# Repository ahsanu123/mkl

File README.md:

# MKL

my kicad libraries

### Reference 

- [easyeda 2 kicad](https://github.com/uPesy/easyeda2kicad.py)
- [Pi Zero Template](https://github.com/vasya-zh/PiZeroHat/tree/main)

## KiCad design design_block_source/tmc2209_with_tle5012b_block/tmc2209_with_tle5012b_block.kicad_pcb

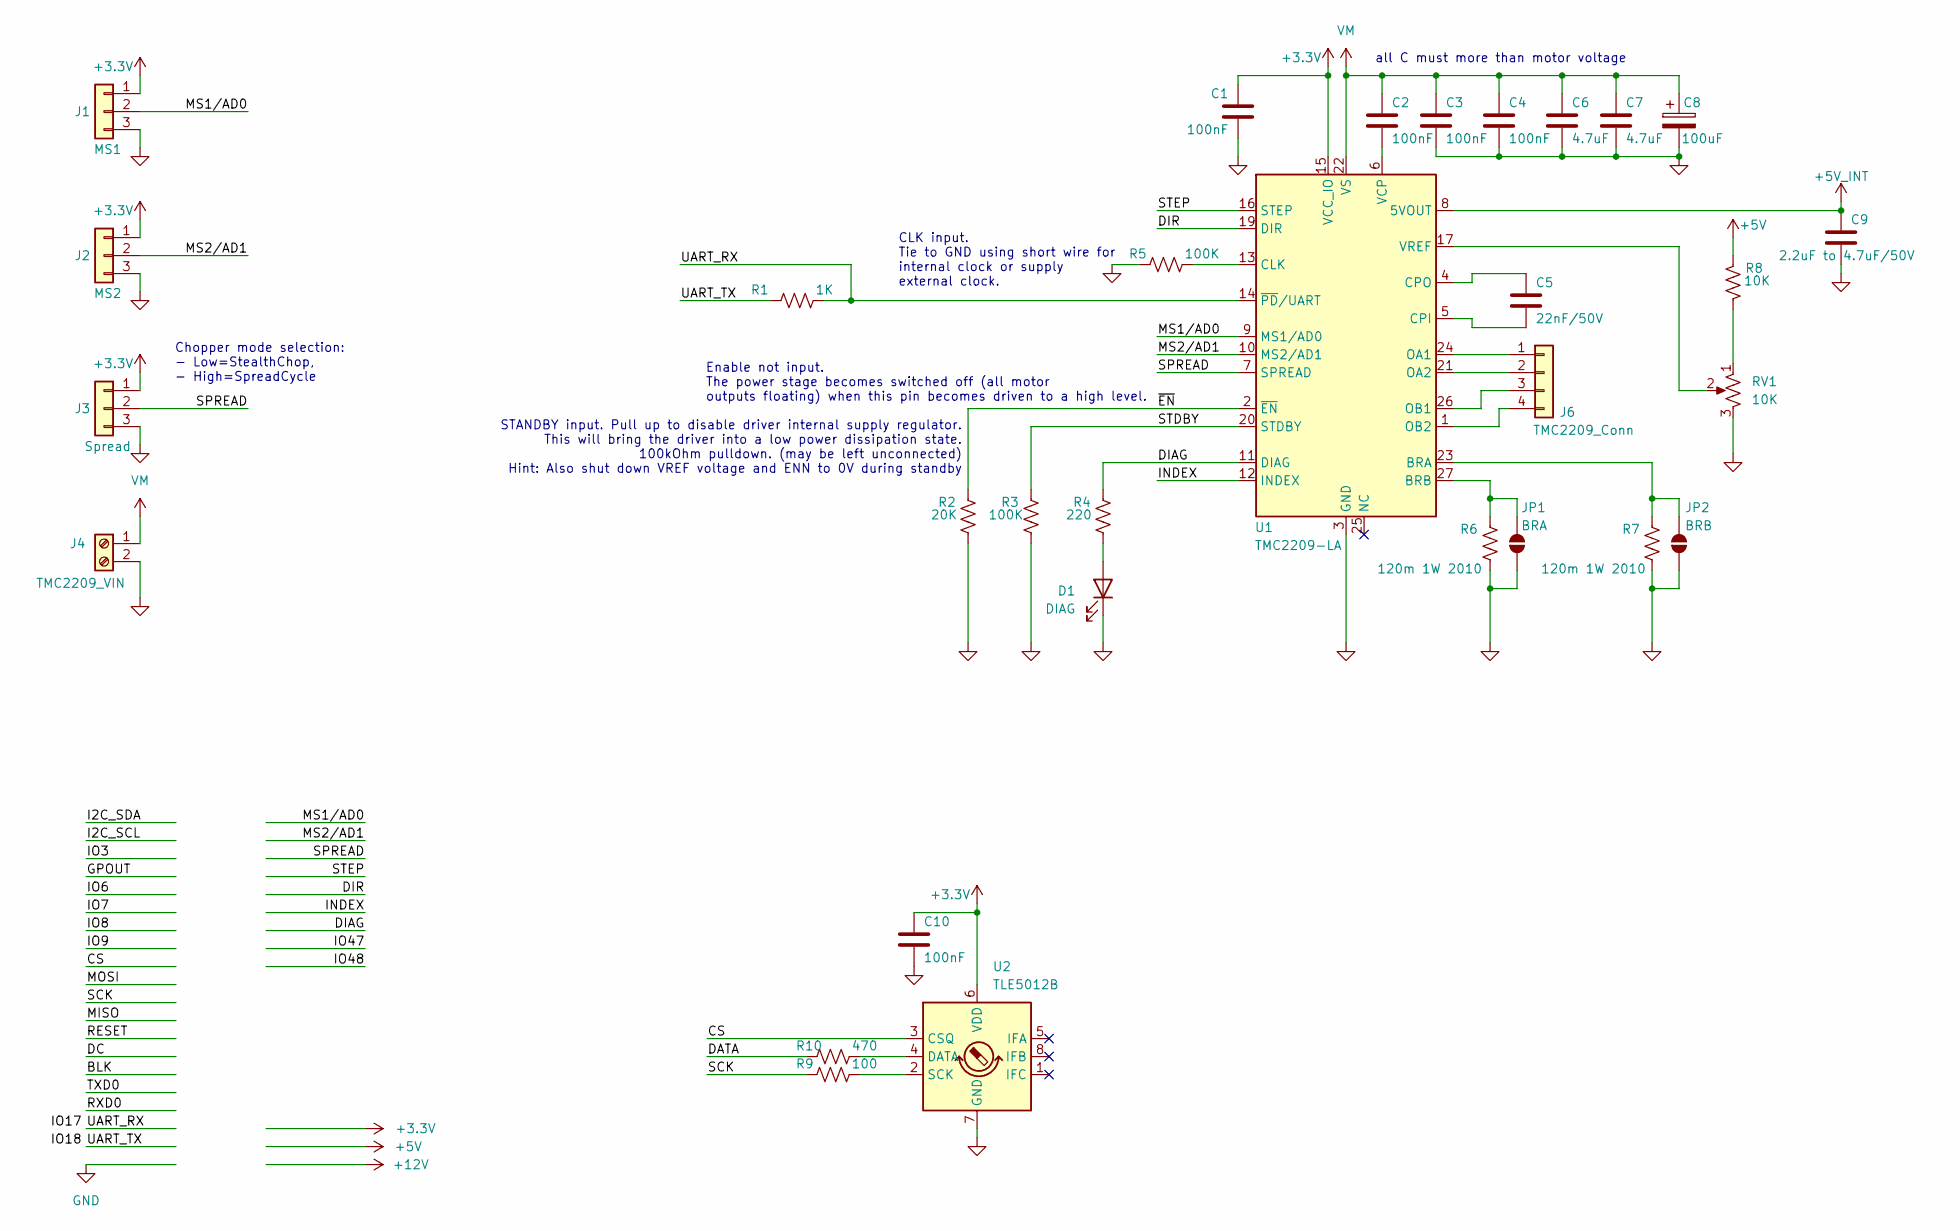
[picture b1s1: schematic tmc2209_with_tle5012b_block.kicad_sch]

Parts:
C1, C2, C3, C4, C10: 100nF; C_0805_2012Metric_Pad1.18x1.45mm_HandSolder
C5: 22nF/50V; C_0805_2012Metric_Pad1.18x1.45mm_HandSolder
C6, C7: 4.7uF; C_0805_2012Metric_Pad1.18x1.45mm_HandSolder
C8: 100uF; CP_Radial_D8.0mm_P3.50mm
C9: 2.2uF to 4.7uF/50V; C_0805_2012Metric_Pad1.18x1.45mm_HandSolder
D1: DIAG; LED_0805_2012Metric_Pad1.15x1.40mm_HandSolder
J1: MS1; PinHeader_1x03_P2.54mm_Vertical
J2: MS2; PinHeader_1x03_P2.54mm_Vertical
J3: Spread; PinHeader_1x03_P2.54mm_Vertical
J4: TMC2209_VIN; TerminalBlock_Phoenix_PT-1,5-2-5.0-H_1x02_P5.00mm_Horizontal
J6: TMC2209_Conn; Molex_Nano-Fit_105313-xx04_1x04_P2.50mm_Horizontal
JP1: BRA; SolderJumper-2_P1.3mm_Open_RoundedPad1.0x1.5mm
JP2: BRB; SolderJumper-2_P1.3mm_Open_RoundedPad1.0x1.5mm
R1: 1K; R_0805_2012Metric_Pad1.20x1.40mm_HandSolder
R2: 20K; R_0805_2012Metric_Pad1.20x1.40mm_HandSolder
R3, R5: 100K; R_0805_2012Metric_Pad1.20x1.40mm_HandSolder
R4: 220; R_0805_2012Metric_Pad1.20x1.40mm_HandSolder
R6, R7: 120m 1W 2010; R_2010_5025Metric
R8: 10K; R_0805_2012Metric_Pad1.20x1.40mm_HandSolder
R9: 100; R_0805_2012Metric_Pad1.20x1.40mm_HandSolder
R10: 470; R_0805_2012Metric_Pad1.20x1.40mm_HandSolder
RV1: 10K; Potentiometer_Bourns_3269W_Vertical
U1: TMC2209-LA; VQFN-28-1EP_5x5mm_P0.5mm_EP3.7x3.7mm
U2: TLE5012B; SOIC-8_3.9x4.9mm_P1.27mm

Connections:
+3.3V: C1.1, C10.1, J1.1, J2.1, J3.1, U1.15 (VCC_IO), U2.6 (VDD)
+5V: R8.1
+5V_INT: C9.1, U1.8 (5VOUT)
/CS: U2.3 (CSQ)
/DATA: R10.2
/DIAG: R4.1, U1.11 (DIAG)
/DIR: U1.19 (DIR)
/INDEX: U1.12 (INDEX)
/MS1/AD0: J1.2, U1.9 (MS1/AD0)
/MS2/AD1: J2.2, U1.10 (MS2/AD1)
/SCK: R9.2
/SPREAD: J3.2, U1.7 (SPREAD)
/STDBY: R3.1, U1.20 (STDBY)
/STEP: U1.16 (STEP)
/UART_RX: R1.1, U1.14 (~PD/UART)
/UART_TX: R1.2
/~EN: R2.1, U1.2 (~EN)
GND: C1.2, C3.2, C4.2, C6.2, C7.2, C8.2, C9.2, C10.2, D1.1 (K), J1.3, J2.3, J3.3, J4.2, JP1.1 (A), JP2.1 (A), R2.2, R3.2, R5.2, R6.2, R7.2, RV1.3, U1.3 (GND), U1.18 (GND), U1.29 (GND), U2.7 (GND)
unnamed: D1.2 (A), R4.2
unnamed: J6.1, U1.24 (OA1)
unnamed: J6.2, U1.21 (OA2)
unnamed: J6.3, U1.26 (OB1)
unnamed: J6.4, U1.1 (OB2)
unnamed: JP1.2 (B), R6.1, U1.27 (BRB)
unnamed: JP2.2 (B), R7.1, U1.23 (BRA)
unnamed: R8.2, RV1.1
unnamed: R5.1, U1.13 (CLK)
unnamed: C5.2, U1.5 (CPI)
unnamed: C5.1, U1.4 (CPO)
unnamed: C2.2, U1.6 (VCP)
unnamed: RV1.2, U1.17 (VREF)
unnamed: R10.1, U2.4 (DATA)
unnamed: R9.1, U2.2 (SCK)
VM: C2.1, C3.1, C4.1, C6.1, C7.1, C8.1, J4.1, U1.22 (VS), U1.28 (VS)

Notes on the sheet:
Chopper mode selection: - Low=StealthChop, - High=SpreadCycle
all C must more than motor voltage
Enable not input. The power stage becomes switched off (all motor outputs floating) when this pin becomes driven to a high level.
STANDBY input. Pull up to disable driver internal supply regulator. This will bring the driver into a low power dissipation state. 100kOhm pulldown. (may be left unconnected) Hint: Also shut down VREF voltage and ENN to 0V during standby
CLK input. Tie to GND using short wire for internal clock or supply external clock.

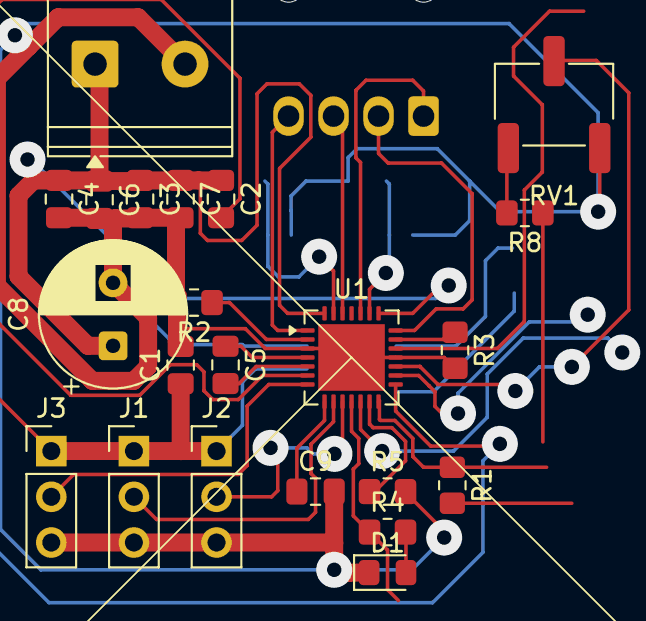
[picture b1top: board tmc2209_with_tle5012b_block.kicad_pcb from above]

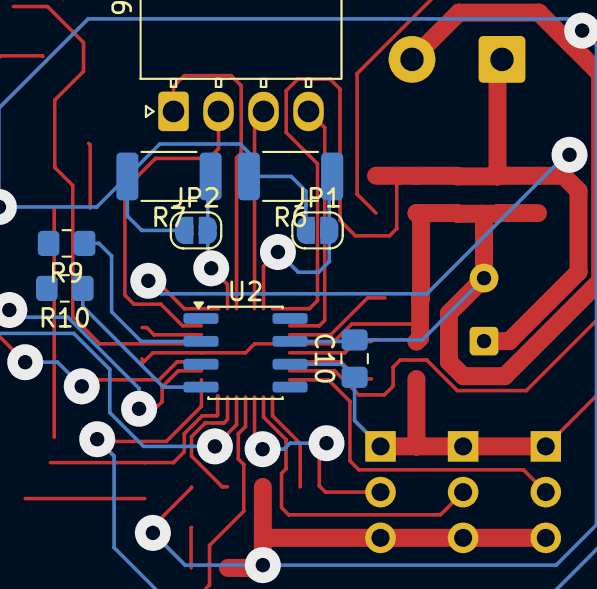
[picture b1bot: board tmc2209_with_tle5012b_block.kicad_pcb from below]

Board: 2 copper layers, 31 parts (9 on the bottom side), 26 nets.

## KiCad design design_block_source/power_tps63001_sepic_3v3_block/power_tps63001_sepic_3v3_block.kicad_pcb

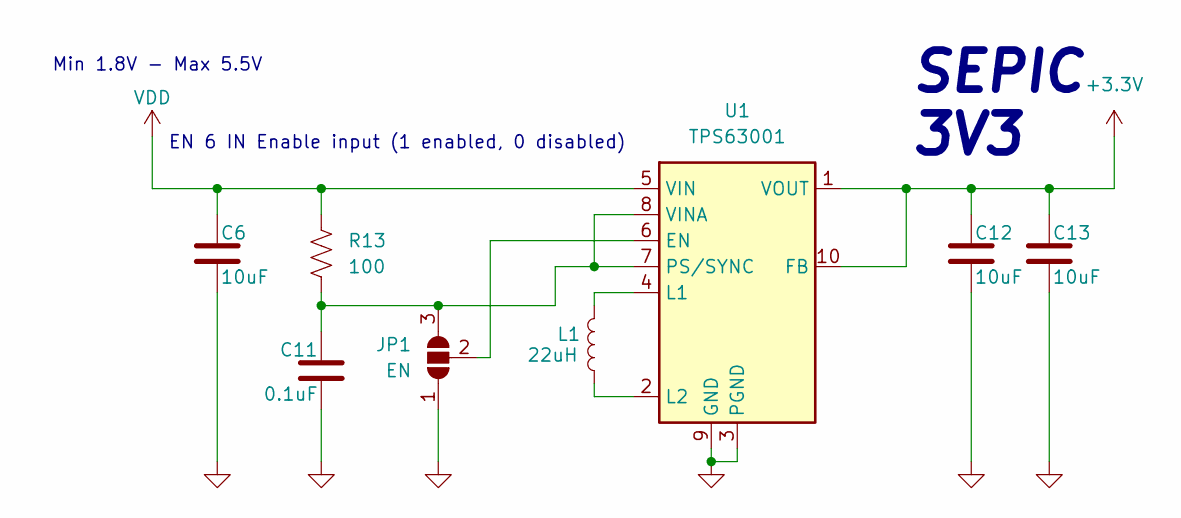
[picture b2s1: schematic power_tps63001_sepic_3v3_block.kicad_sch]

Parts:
C6, C12, C13: 10uF; C_0805_2012Metric_Pad1.18x1.45mm_HandSolder
C11: 0.1uF; C_0805_2012Metric_Pad1.18x1.45mm_HandSolder
JP1: EN; SolderJumper-3_P1.3mm_Open_RoundedPad1.0x1.5mm_NumberLabels
L1: 22uH; L_Bourns_SRP7028A_7.3x6.6mm
R13: 100; R_0805_2012Metric_Pad1.20x1.40mm_HandSolder
U1: TPS63001; Texas_DRC0010J_ThermalVias

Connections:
+3.3V: C12.1, C13.1, U1.1 (VOUT), U1.10 (FB)
GND: C6.2, C11.2, C12.2, C13.2, JP1.1 (A), U1.3 (PGND), U1.9 (GND), U1.11 (PGND)
unnamed: C11.1, JP1.3 (B), R13.2, U1.7 (PS/SYNC), U1.8 (VINA)
unnamed: JP1.2 (C), U1.6 (EN)
unnamed: L1.2, U1.4 (L1)
unnamed: L1.1, U1.2 (L2)
VDD: C6.1, R13.1, U1.5 (VIN)

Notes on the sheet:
SEPIC 3V3
Min 1.8V - Max 5.5V
EN 6 IN Enable input (1 enabled, 0 disabled)

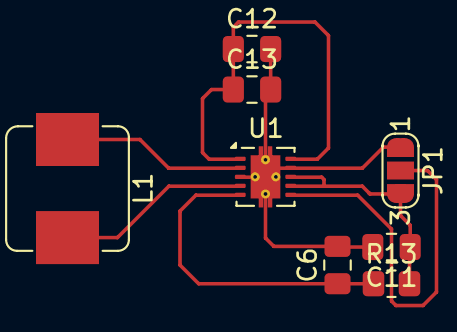
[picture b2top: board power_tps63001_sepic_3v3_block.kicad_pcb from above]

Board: 2 copper layers, 8 parts (0 on the bottom side), 7 nets.

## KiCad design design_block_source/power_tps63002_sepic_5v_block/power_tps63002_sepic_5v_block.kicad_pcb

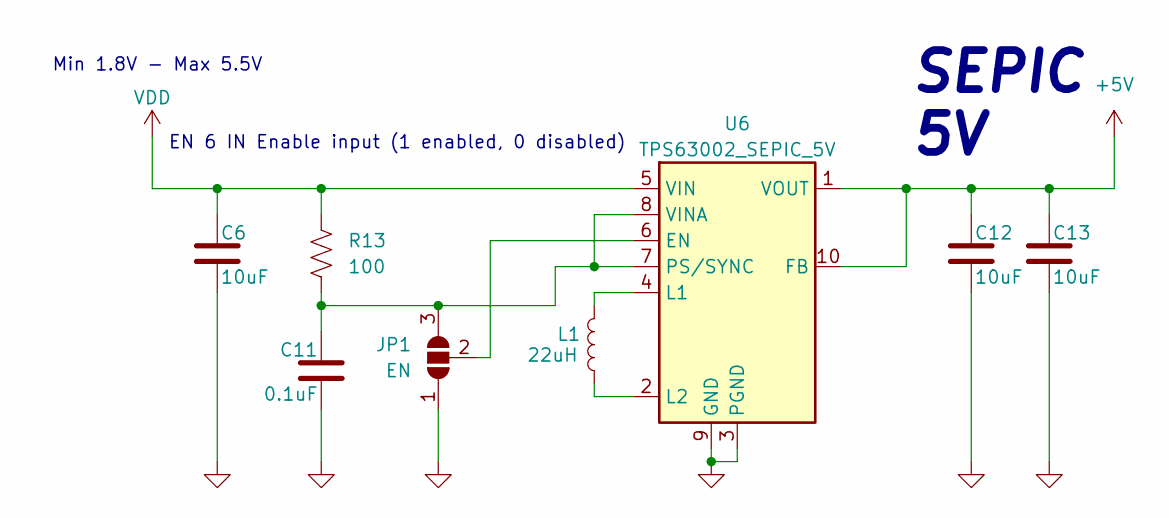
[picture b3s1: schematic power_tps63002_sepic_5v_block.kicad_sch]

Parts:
C6, C12, C13: 10uF; C_0805_2012Metric_Pad1.18x1.45mm_HandSolder
C11: 0.1uF; C_0805_2012Metric_Pad1.18x1.45mm_HandSolder
JP1: EN; SolderJumper-3_P1.3mm_Open_RoundedPad1.0x1.5mm_NumberLabels
L1: 22uH; L_Bourns_SRP7028A_7.3x6.6mm
R13: 100; R_0805_2012Metric_Pad1.20x1.40mm_HandSolder
U6: TPS63002_SEPIC_5V; Texas_DRC0010J_ThermalVias

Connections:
+5V: C12.1, C13.1, U6.1 (VOUT), U6.10 (FB)
GND: C6.2, C11.2, C12.2, C13.2, JP1.1 (A), U6.3 (PGND), U6.9 (GND), U6.11 (PGND)
unnamed: C11.1, JP1.3 (B), R13.2, U6.7 (PS/SYNC), U6.8 (VINA)
unnamed: JP1.2 (C), U6.6 (EN)
unnamed: L1.2, U6.4 (L1)
unnamed: L1.1, U6.2 (L2)
VDD: C6.1, R13.1, U6.5 (VIN)

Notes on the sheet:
SEPIC 5V
Min 1.8V - Max 5.5V
EN 6 IN Enable input (1 enabled, 0 disabled)

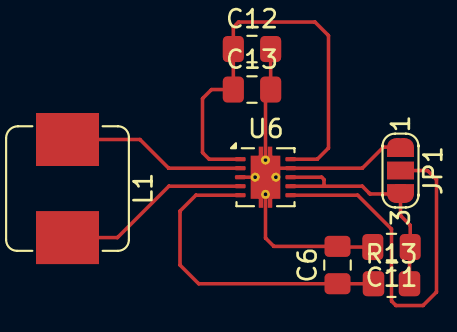
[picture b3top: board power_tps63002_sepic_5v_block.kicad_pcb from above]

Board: 2 copper layers, 8 parts (0 on the bottom side), 7 nets.

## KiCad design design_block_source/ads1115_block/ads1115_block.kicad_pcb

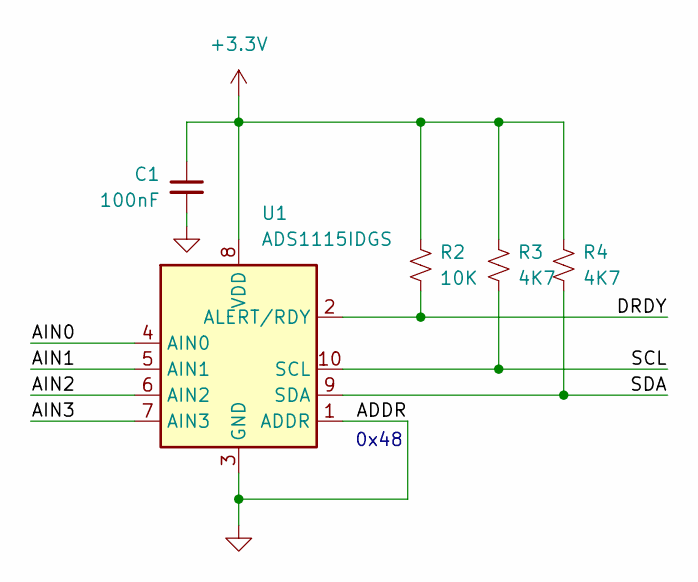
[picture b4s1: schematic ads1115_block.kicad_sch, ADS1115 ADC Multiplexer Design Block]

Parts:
C1: 100nF; C_0805_2012Metric
R2: 10K; R_0805_2012Metric
R3, R4: 4K7; R_0805_2012Metric
U1: ADS1115IDGS; TSSOP-10_3x3mm_P0.5mm

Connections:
+3.3V: C1.1, R2.1, R3.1, R4.1, U1.8 (VDD)
/AIN0: U1.4 (AIN0)
/AIN1: U1.5 (AIN1)
/AIN2: U1.6 (AIN2)
/AIN3: U1.7 (AIN3)
/DRDY: R2.2, U1.2 (ALERT/RDY)
/SCL: R3.2, U1.10 (SCL)
/SDA: R4.2, U1.9 (SDA)
GND: C1.2, U1.1 (ADDR), U1.3 (GND)

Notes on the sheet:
0x48

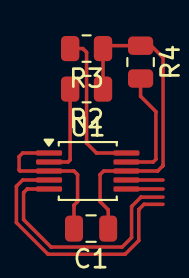
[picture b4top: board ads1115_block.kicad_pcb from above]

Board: 2 copper layers, 5 parts (0 on the bottom side), 5 nets.

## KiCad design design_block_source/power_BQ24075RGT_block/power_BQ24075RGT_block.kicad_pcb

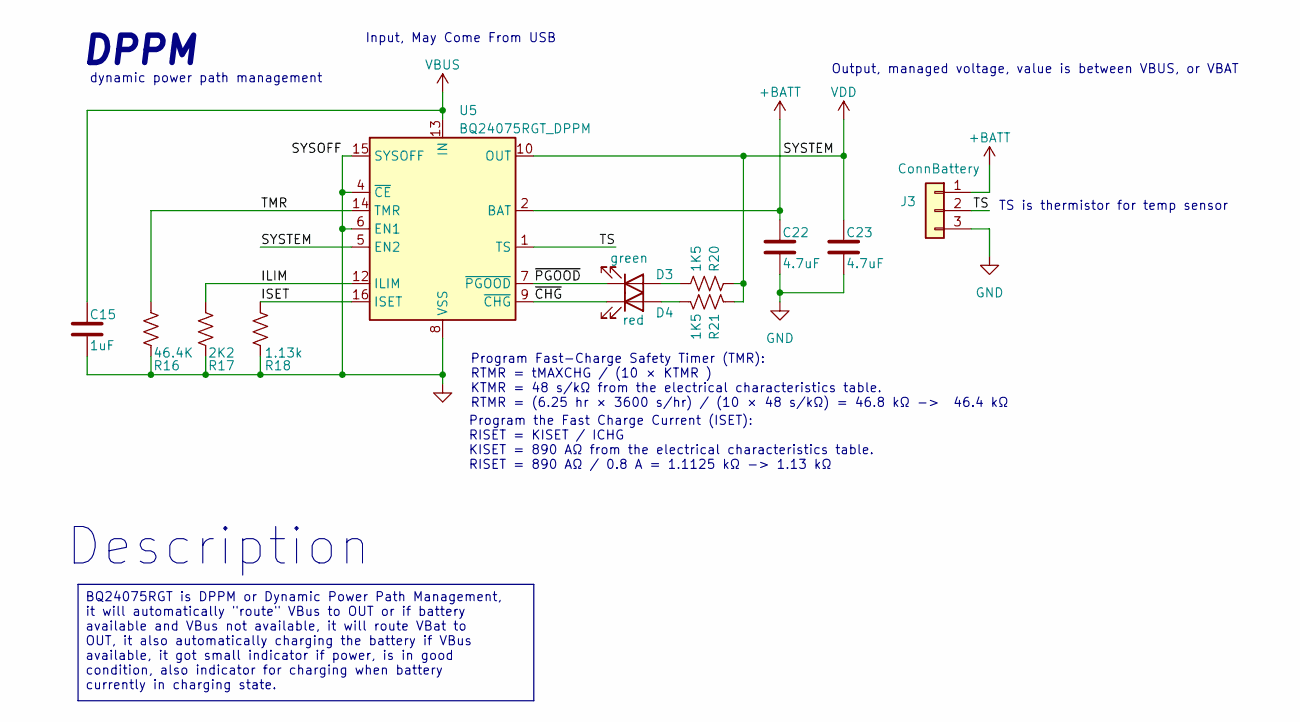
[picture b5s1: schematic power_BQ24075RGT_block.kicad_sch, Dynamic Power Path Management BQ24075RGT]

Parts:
C15: 1uF; C_0805_2012Metric_Pad1.18x1.45mm_HandSolder
C22, C23: 4.7uF; C_0805_2012Metric_Pad1.18x1.45mm_HandSolder
D3: green; LED_0805_2012Metric_Pad1.15x1.40mm_HandSolder
D4: red; LED_0805_2012Metric_Pad1.15x1.40mm_HandSolder
J3: ConnBattery; PinHeader_1x03_P2.54mm_Vertical
R16: 46.4K; R_0805_2012Metric_Pad1.20x1.40mm_HandSolder
R17: 2K2; R_0805_2012Metric_Pad1.20x1.40mm_HandSolder
R18: 1.13k; R_0805_2012Metric_Pad1.20x1.40mm_HandSolder
R20, R21: 1K5; R_0805_2012Metric_Pad1.20x1.40mm_HandSolder
U5: BQ24075RGT_DPPM; VQFN-16-1EP_3x3mm_P0.5mm_EP1.6x1.6mm

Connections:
+BATT: C22.1, J3.1, U5.2 (BAT), U5.3 (BAT)
/ILIM: R17.1, U5.12 (ILIM)
/ISET: R18.1, U5.16 (ISET)
/TMR: R16.1, U5.14 (TMR)
/TS: J3.2, U5.1 (TS)
/~CHG: D4.1 (K), U5.9 (~CHG)
/~PGOOD: D3.1 (K), U5.7 (~PGOOD)
GND: C15.2, C22.2, C23.2, J3.3, R16.2, R17.2, R18.2, U5.4 (~CE), U5.6 (EN1), U5.8 (VSS), U5.15 (SYSOFF), U5.17 (VSS)
unnamed: D3.2 (A), R20.1
unnamed: D4.2 (A), R21.1
VBUS: C15.1, U5.13 (IN)
VDD: C23.1, R20.2, R21.2, U5.5 (EN2), U5.10 (OUT), U5.11 (OUT)

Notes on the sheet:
Output, managed voltage, value is between VBUS, or VBAT
DPPM
dynamic power path management
Input, May Come From USB
Program the Fast Charge Current (ISET): RISET = KISET / ICHG KISET = 890 AΩ from the electrical characteristics table. RISET = 890 AΩ / 0.8 A = 1.1125 kΩ -> 1.13 kΩ
Program Fast-Charge Safety Timer (TMR): RTMR = tMAXCHG / (10 × KTMR ) KTMR = 48 s/kΩ from the electrical characteristics table. RTMR = (6.25 hr × 3600 s/hr) / (10 × 48 s/kΩ) = 46.8 kΩ -> 46.4 kΩ
Description
TS is thermistor for temp sensor
BQ24075RGT is DPPM or Dynamic Power Path Management, it will automatically "route" VBus to OUT or if battery available and VBus not available, it will route VBat to OUT, it also automatically charging the battery if VBus available, it got small indicator if power, is in good condition, also indicat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

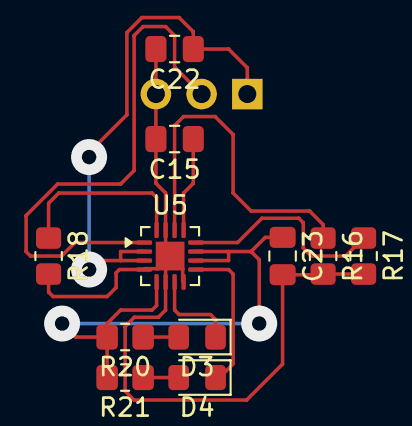
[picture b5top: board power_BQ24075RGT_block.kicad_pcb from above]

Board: 2 copper layers, 12 parts (1 on the bottom side), 12 nets.

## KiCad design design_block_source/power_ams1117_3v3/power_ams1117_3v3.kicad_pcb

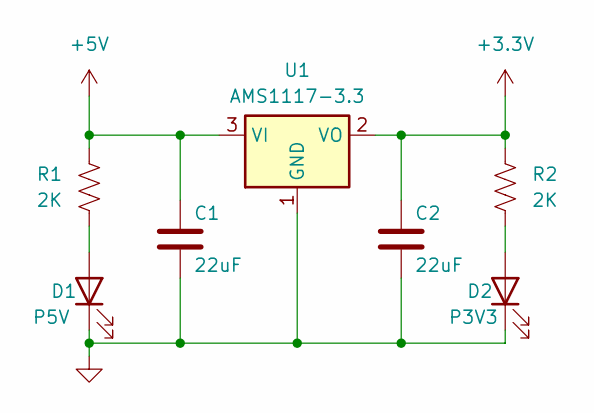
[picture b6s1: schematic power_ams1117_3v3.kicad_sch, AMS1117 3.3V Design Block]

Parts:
C1, C2: 22uF; C_0805_2012Metric_Pad1.18x1.45mm_HandSolder
D1: P5V; LED_1206_3216Metric_Pad1.42x1.75mm_HandSolder
D2: P3V3; LED_1206_3216Metric_Pad1.42x1.75mm_HandSolder
R1, R2: 2K; R_0805_2012Metric_Pad1.20x1.40mm_HandSolder
U1: AMS1117-3.3; SOT-223-3_TabPin2

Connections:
+3.3V: C2.1, R2.1, U1.2 (VO)
+5V: C1.1, R1.1, U1.3 (VI)
GND: C1.2, C2.2, D1.1 (K), D2.1 (K), U1.1 (GND)
unnamed: D1.2 (A), R1.2
unnamed: D2.2 (A), R2.2

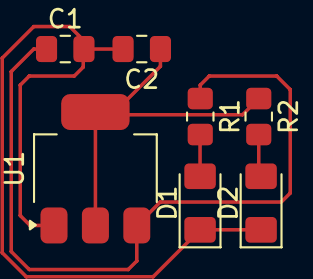
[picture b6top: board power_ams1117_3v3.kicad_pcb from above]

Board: 2 copper layers, 7 parts (0 on the bottom side), 5 nets.

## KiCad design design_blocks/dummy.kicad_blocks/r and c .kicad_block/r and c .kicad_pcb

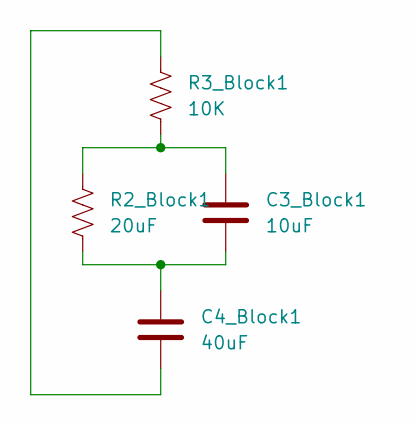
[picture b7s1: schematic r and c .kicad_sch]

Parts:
C3_Block1: 10uF; C_Rect_L11.0mm_W4.3mm_P10.00mm_MKT
C4_Block1: 40uF; C_Rect_L11.0mm_W4.3mm_P10.00mm_MKT
R2_Block1: 20uF; R_0805_2012Metric
R3_Block1: 10K; R_0805_2012Metric

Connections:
unnamed: C3_Block1.1, R2_Block1.1, R3_Block1.2
unnamed: C3_Block1.2, C4_Block1.1, R2_Block1.2
unnamed: C4_Block1.2, R3_Block1.1

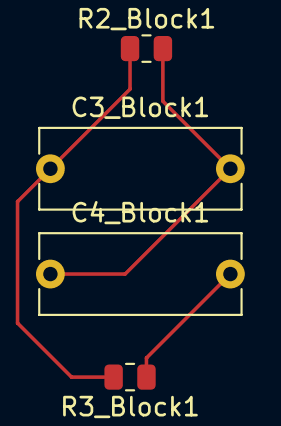
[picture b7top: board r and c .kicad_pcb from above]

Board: 2 copper layers, 4 parts (0 on the bottom side), 3 nets.

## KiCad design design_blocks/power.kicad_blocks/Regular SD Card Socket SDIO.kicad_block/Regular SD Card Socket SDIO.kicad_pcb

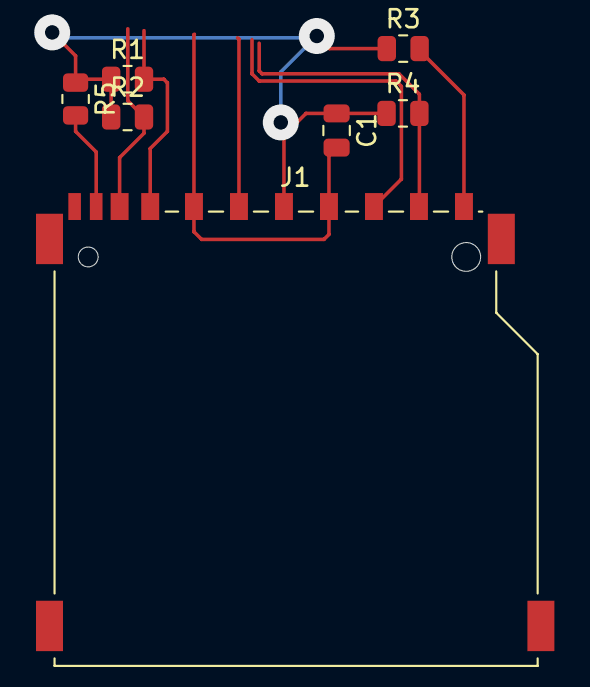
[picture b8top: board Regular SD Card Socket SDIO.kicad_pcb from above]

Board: 2 copper layers, 7 parts (0 on the bottom side), 7 nets.

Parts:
C1: 100nF; C_0805_2012Metric
J1: SD_Card_Receptacle; SD_TE_2041021
R1, R2, R3, R4, R5: 47K; R_0805_2012Metric

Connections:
+3.3V: C1.1, J1.4 (VDD), R1.1, R2.1, R3.1, R4.1, R5.1
/CARD_DETECT: J1.10 (CARD_DETECT), R5.2
/DAT0: J1.7 (DAT0), R1.2
/DAT1: J1.8 (DAT1), R2.2
/DAT2: J1.9 (DAT2), R3.2
/DAT3: J1.1 (CD/DAT3), R4.2
GND: C1.2, J1.3 (VSS), J1.6 (VSS)

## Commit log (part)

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2026-04-22 init mkl
2026-04-22 feat: add pi zero template
2026-04-22 add TI CD4043BDR
2026-04-28 add keyboard footprint library
2026-04-28 add easy to get microsd card
2026-04-28 add 22d18d2
